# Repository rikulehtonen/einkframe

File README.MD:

# E-ink Art Frame - Low-Power Picture Display

A low-power digital art frame that cycles through images stored on an SD card, displayed on a 6-color e-paper screen. The display retains its image indefinitely without power, making it ideal for an always-on picture frame. Supports both Waveshare and Pimoroni Inky Impression panels.

## Features

- Cycles through images stored on a microSD card
- 6-color e-paper display: black, white, yellow, red, blue, green
- Ultra-low power — display holds image without power between updates
- Three firmware variants: 4-inch Arduino R4, 13.3-inch Waveshare ESP32, 13.3-inch Inky Impression ESP32
- Custom PCB hardware designs included

---

## Hardware Variants

### 4-inch (Waveshare EPD-4in0e) — Arduino R4
- **Resolution:** 400 × 600 px
- **Controller:** Arduino UNO R4
- **Update interval:** every 4 minutes
- Firmware: [waweshare_Arduino_R4_4inch/](waweshare_Arduino_R4_4inch/)

### 13.3-inch (Waveshare EPD-13in3e) — ESP32
- **Resolution:** 1200 × 1600 px
- **Controller:** ESP32 (with PSRAM)
- **Update interval:** every 13 hours (deep sleep between updates)
- Firmware: [waweshare_ESP32_13inch/](waweshare_ESP32_13inch/)

### 13.3-inch (Pimoroni Inky Impression) — ESP32
- **Resolution:** 1200 × 1600 px
- **Controller:** ESP32 (with PSRAM)
- **Update interval:** every 13 hours (deep sleep between updates)
- **Display:** Pimoroni Inky Impression 13.3" (uses the same underlying panel as the Waveshare variant)
- **Difference from Waveshare variant:** skips the initial screen clear before rendering, avoiding a full white flash on each update
- Firmware: [inky_ESP32_13inch/](inky_ESP32_13inch/)

---

## Repository Structure

```
├── waweshare_Arduino_R4_4inch/   # Arduino R4 firmware for 4-inch Waveshare display
├── waweshare_ESP32_13inch/       # ESP32 firmware for 13-inch Waveshare display
├── inky_ESP32_13inch/            # ESP32 firmware for 13-inch Pimoroni Inky Impression
├── image_conversion/             # Python script to convert images for the display
│   ├── convert.py
│   ├── input/                    # Place source PNG files here
│   └── output/                   # Converted .bin files are written here
├── hardware/
│   ├── controller/               # KiCad controller PCB design + gerbers
│   └── shield/                   # KiCad shield PCB design
├── documentation/                # Waveshare datasheets and manuals
└── demo/                         # Vendor-provided reference demos
```

---

## Getting Started

### 1. Convert Images

Images must be pre-converted to a packed binary format before being loaded onto the SD card.

**Requirements:** Python 3, Pillow (`pip install Pillow`)

```bash
cd image_conversion
# Place your PNG files in the input/ folder
python convert.py
# Output .bin files will appear in output/
```

The script quantizes each image to the 6-color palette, then packs 2 pixels per byte (4 bits each) to produce a `.bin` file. A palette-quantized `.bmp` preview is also saved alongside each `.bin`.

**Image dimensions must match the display:**
- 4-inch: 400 × 600 px
- 13-inch: 1200 × 1600 px

### 2. Prepare the SD Card

Copy the converted `.bin` files to the root of a FAT32-formatted microSD card, then create two text files:

**`files.txt`** — comma-separated list of filenames to display:
```
image1.bin,image2.bin,image3.bin
```

**`config.txt`** — current image index (start with `0`):
```
0
```

The firmware reads the current index from `config.txt`, displays that image, increments the index (wrapping around at the end of the list), and writes it back before sleeping.

### 3. Flash the Firmware

Open the appropriate sketch in the Arduino IDE:
- **4-inch Waveshare:** `waweshare_Arduino_R4_4inch/Arduino_R4_4inch.ino`
- **13-inch Waveshare:** `waweshare_ESP32_13inch/waweshare_ESP32_13inch.ino`
- **13-inch Inky Impression:** `inky_ESP32_13inch/inky_ESP32_13inch.ino`

Flash to your board using the Arduino IDE.

---

## Pin Connections

### Arduino R4 (4-inch display)

| Signal   | Arduino Pin |
|----------|-------------|
| SCK      | 13          |
| MOSI     | 11          |
| EPD CS   | 10          |
| DC       | 9           |
| RST      | 8           |
| BUSY     | 7           |
| PWR      | 6           |
| SD CS    | 4           |

### ESP32 (13-inch Waveshare and Inky Impression — same pins)

| Signal   | ESP32 Pin |
|----------|-----------|
| SCK      | 18        |
| MOSI     | 23        |
| MISO     | 19        |
| EPD CS_M | 2         |
| EPD CS_S | 13        |
| DC       | 14        |
| RST      | 0         |
| BUSY     | 26        |
| PWR      | 25        |
| SD CS    | 17        |

The 13-inch display uses dual SPI chip selects (CS_M and CS_S) to address the left and right halves of the panel independently.

---

## Color Palette

| Color  | 3-bit Code | RGB            |
|--------|-----------|----------------|
| Black  | `0x0`     | (0, 0, 0)      |
| White  | `0x1`     | (255, 255, 255)|
| Yellow | `0x2`     | (255, 255, 0)  |
| Red    | `0x3`     | (255, 0, 0)    |
| Blue   | `0x5`     | (0, 0, 255)    |
| Green  | `0x6`     | (0, 255, 0)    |

Pixels are packed two per byte: `[pixel_n (4 bits) | pixel_n+1 (4 bits)]`.

---

## Hardware

Custom PCB designs are provided in [hardware/](hardware/) (KiCad format):
- **controller/** — main controller board with gerbers ready for fabrication
- **shield/** — e-paper display shield/adapter

Waveshare schematics and datasheets are in [documentation/](documentation/).

---

## Dependencies

- [Waveshare e-Paper Arduino libraries](https://github.com/waveshareteam/e-Paper) (driver files included in each firmware folder)
- Arduino IDE with ESP32 board support (for 13-inch variant)
- Arduino UNO R4 board support (for 4-inch variant)
- Python + Pillow (for image conversion)

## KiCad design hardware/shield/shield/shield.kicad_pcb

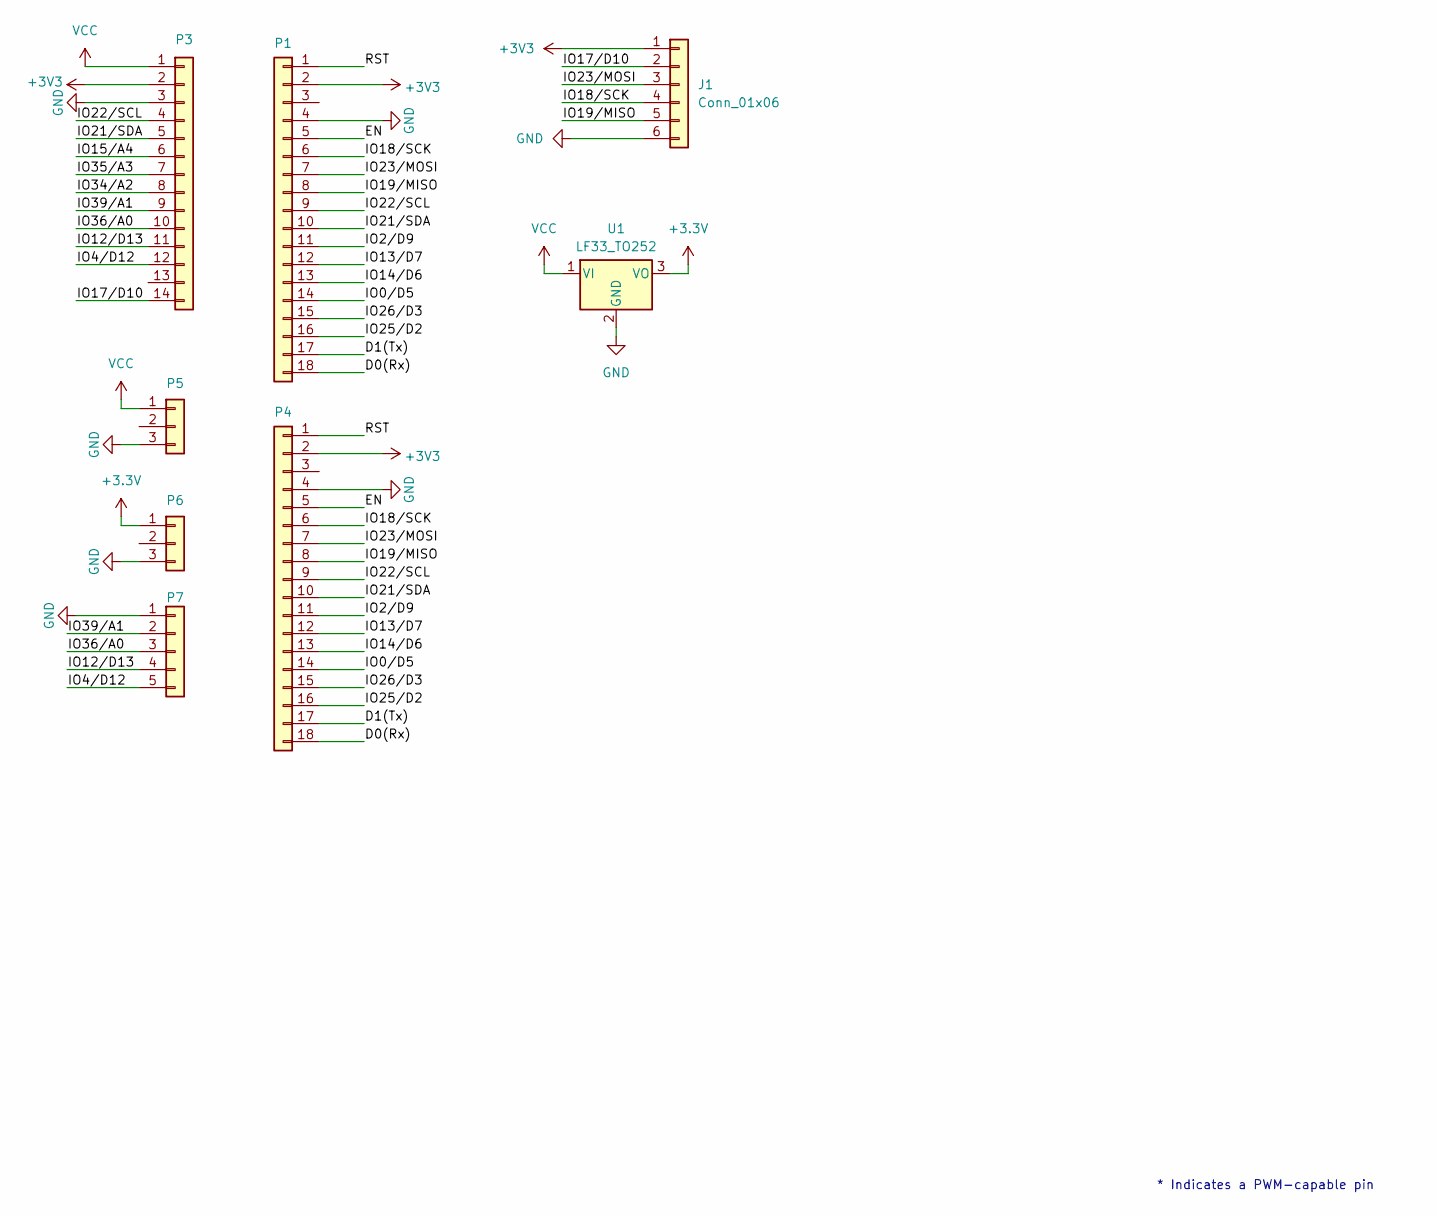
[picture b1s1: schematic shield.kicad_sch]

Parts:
J1: Conn_01x06; PinHeader_1x06_P2.54mm_Horizontal
P1: Digital/PWM; PinSocket_1x18_P2.54mm_Vertical
P3: PinSocket_1x14_P2.54mm_Vertical
P4: Digital/PWM; PinHeader_1x18_P2.54mm_Horizontal
P5, P6: PinHeader_1x03_P2.54mm_Horizontal
P7: PinHeader_1x05_P2.54mm_Horizontal
U1: LF33_TO252; TO-252-2

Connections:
+3.3V: P6.1, U1.3 (VO)
+3V3: J1.1, P1.2, P3.2, P4.2
/D0(Rx): P1.18, P4.18
/D1(Tx): P1.17, P4.17
/EN: P1.5, P4.5
/IO0/D5: P1.14, P4.14
/IO2/D9: P1.11, P4.11
/IO4/D12: P3.12, P7.5
/IO12/D13: P3.11, P7.4
/IO13/D7: P1.12, P4.12
/IO14/D6: P1.13, P4.13
/IO15/A4: P3.6
/IO17/D10: J1.2, P3.14
/IO18/SCK: J1.4, P1.6, P4.6
/IO19/MISO: J1.5, P1.8, P4.8
/IO21/SDA: P1.10, P3.5, P4.10
/IO22/SCL: P1.9, P3.4, P4.9
/IO23/MOSI: J1.3, P1.7, P4.7
/IO25/D2: P1.16, P4.16
/IO26/D3: P1.15, P4.15
/IO34/A2: P3.8
/IO35/A3: P3.7
/IO36/A0: P3.10, P7.3
/IO39/A1: P3.9, P7.2
/RST: P1.1, P4.1
GND: J1.6, P1.4, P3.3, P4.4, P5.3, P6.3, P7.1, U1.2 (GND)
VCC: P3.1, P5.1, U1.1 (VI)

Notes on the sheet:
* Indicates a PWM-capable pin

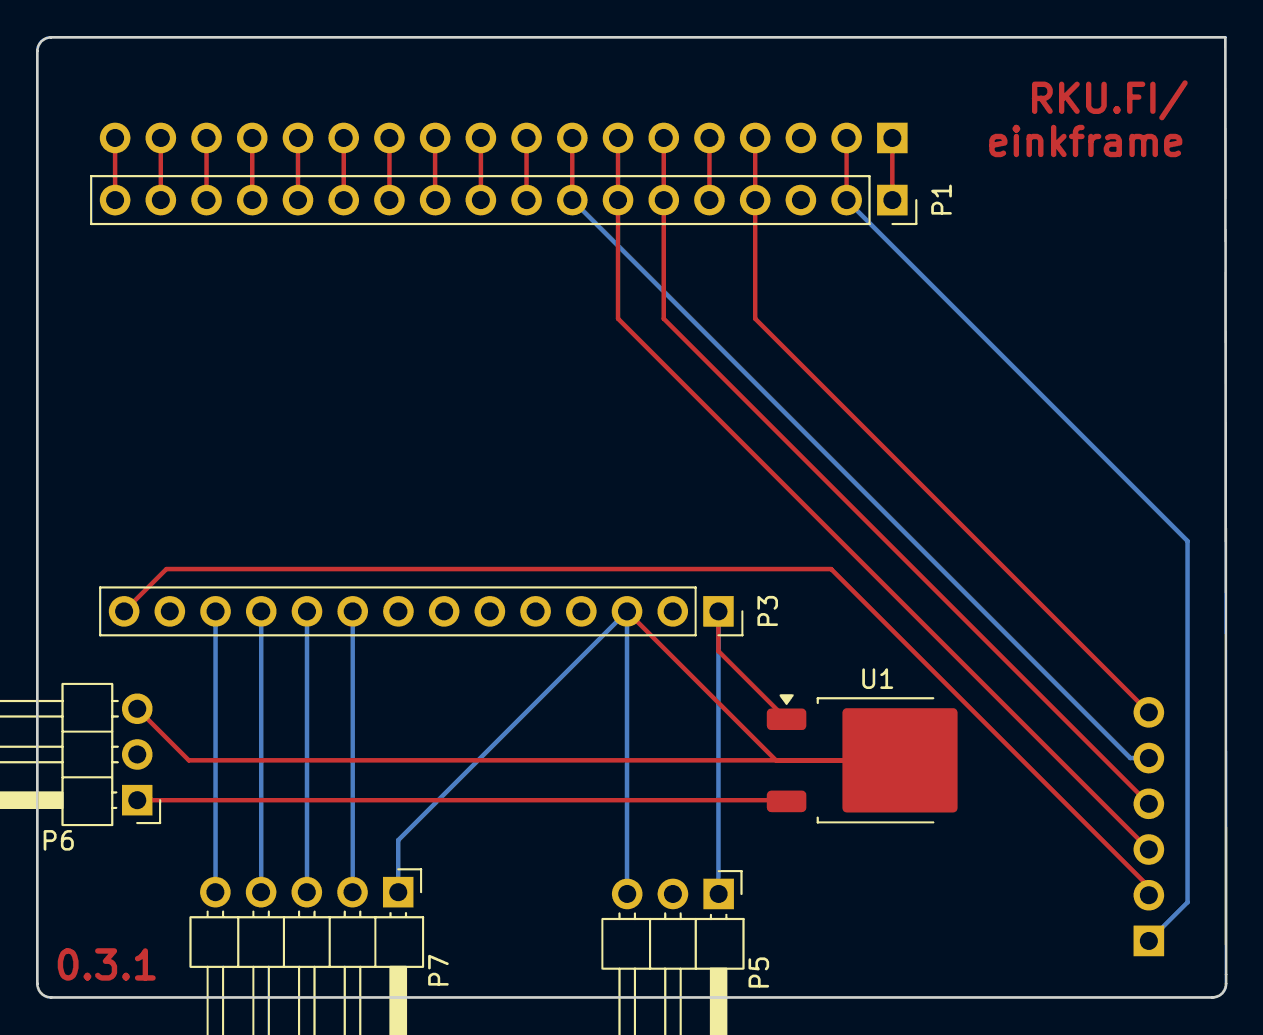
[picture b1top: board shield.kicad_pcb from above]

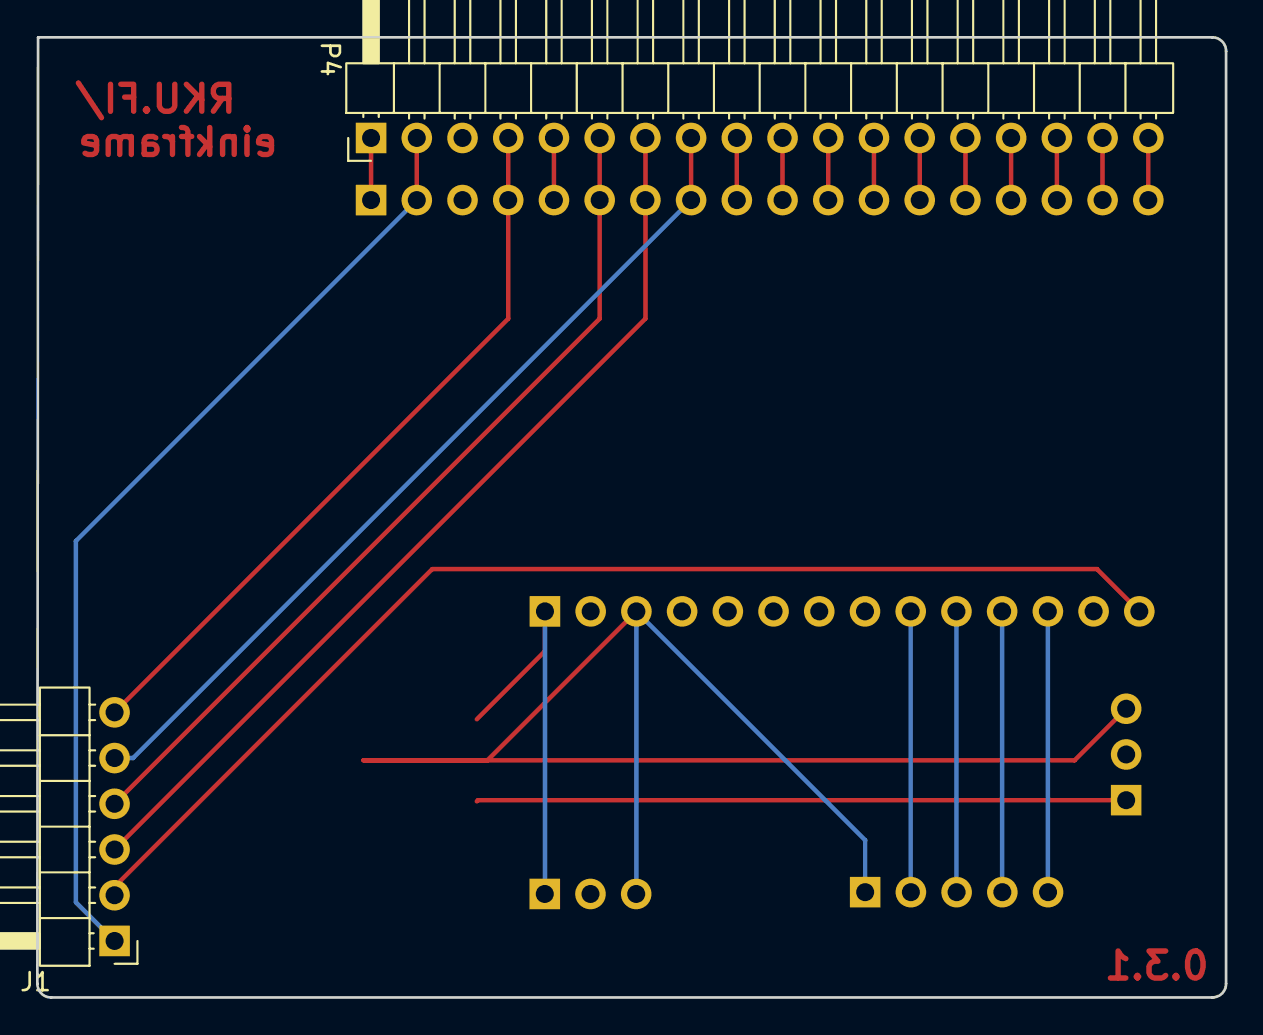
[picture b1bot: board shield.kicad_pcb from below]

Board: 2 copper layers, 66.0 x 53.3 mm, 8 parts (2 on the bottom side), 24 nets.

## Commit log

2025-10-25 Init folders
2025-10-25 rename file
2025-10-25 combine readme
2025-10-25 move font and image files to removed
2025-10-25 code for painting the image from sd card
2025-11-06 rename and define pins
2025-11-11 create file read and write operations
2025-11-12 add sd card reader for esp32
2025-11-12 add image render
2025-11-13 add sd and eink init
2025-11-27 update setup script
2025-11-27 add functions
2025-11-27 remove static from the functions
2025-11-30 restructure the repo
2025-11-30 add debug files
2025-12-07 test different init order
2025-12-07 restructure
2025-12-13 update experiment
2025-12-13 create image update cycle
2025-12-13 fix communication cycle
2025-12-18 Render2 for reference
2025-12-19 debug
2025-12-23 add debug
2025-12-27 restructure demo
2025-12-28 eink update cycle fix
2025-12-28 change buffer len
2025-12-28 add test file
2025-12-29 improve buffer
2026-01-03 modified update cycle
2026-01-06 test the update cycle
2026-01-06 update cycle
2026-01-06 increase buffer size
2026-01-10 read and write to psram
2026-01-10 finalize imageload and paint demo
2026-01-10 update cycle fix
2026-01-10 add documentation
2026-01-10 add retry for sd attach and 12h sleep
2026-01-20 add delay and clear
2026-01-23 add hardware files
2026-01-30 add kicad files
2026-01-31 add pins for in/out
2026-02-01 add gerbers
2026-02-01 add shield 0.3.1 version
2026-02-17 remove backups
2026-02-17 rename demo folders
2026-02-17 rename folders
2026-02-17 add code for inky
2026-02-19 add test code
2026-02-25 modified code for inky
2026-02-25 modifications for clear
2026-02-28 revert clear and display
2026-03-03 fix the init
2026-03-03 fix delay order for debug
2026-03-03 remove unused code
2026-03-03 fix naming
2026-03-18 add simple update
2026-03-22 add simple inky update
2026-03-22 remove debug code
2026-03-31 clean up temp files
2026-03-31 Rename readme
2026-03-31 add pictures
2026-03-31 update pre-release readme
2026-04-25 Clear to white every 5 cycles
